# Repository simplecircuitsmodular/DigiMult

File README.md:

# DigiMult

The DigiMult features 2 DAC outputs, a trigger input, and an analog input as well as 4 potentiometers and a switch. The module can be programmed using the Arduino IDE. 

Shortly after I started designing this module, CCTV announced the Cascadence. Since my design and CCTV's were almost identical, I decided to make this module compatable with theirs. There are only 4 differences between them:
- The DigiMult is all through hole, making it easier to solder.
- The DigiMult is 8hp instead of 4hp. This is due to the larger through hole components.
- The DigiMult feaures an analog input, which is absent from the Cascadence.
- The DigiMult switch is on pin rather than pin to free up an analog pin for the input.

Information on the Cascadence can be found at [CCTV's website](https://www.cctv.fm/product-page/cascadence) and [their GitHub page](https://github.com/cctvfm/cascadence).

A template.ino and information on modifying CCTV's software to work with the DigiMult will be added soon.

## Files
### DigiMult_xx .brd and .sch
These are the board and schematic files needed to manufacture PCBs. Gerbers need to be generated in Eagle for manufacturing.

### DigiMultParts_xx.md
These are the parts lists for each module. A mouser BOM is available in this file as well.

### DigiMult.ai
These are the panels in Adobe Illustrator format. I make my panels on a laser cutter with 1/8 inch acrylic.

## Updates

### 01 07OCT19
Initial upload. Design is currently untested.

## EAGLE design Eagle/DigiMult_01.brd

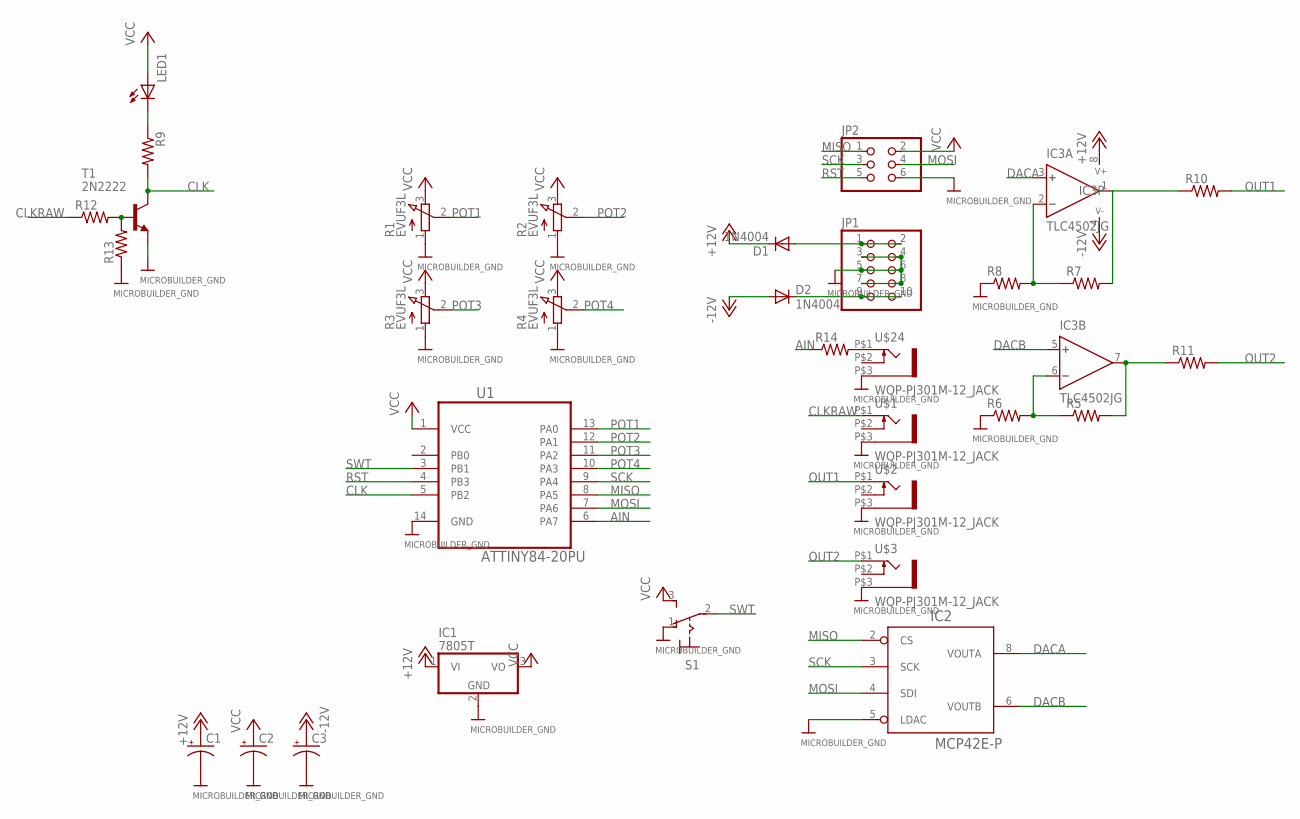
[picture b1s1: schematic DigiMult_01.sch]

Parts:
C1, C2, C3: CPOL-USE2.5-5; E2,5-5
D1, D2: 1N4004; DO41-10
IC1: 7805T; TO220H
IC2: MCP42E-P; DIL08
IC3: TLC4502JG; DIL08
JP1: PINHD-2X5/OCT; 2X05
JP2: PINHD-2X3/OCT; 2X03
LED1: LED3MM
R1, R2, R3, R4: EVUF3L; EVUFXL
R5, R6, R7, R8, R9, R10, R11, R12, R13, R14: R-US_0204/2V; 0204V
S1: M9040P
T1: 2N2222; TO92-EBC-OVAL
U1: ATTINY84-20PU; DIP254P762X533-14
U$1, U$2, U$3, U$24: WQP-PJ301M-12_JACK

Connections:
+12V: C1.+, D1.C, IC1.1 (VI), IC3.8 (V+)
-12V: C3.+, D2.A, IC3.4 (V-)
AIN: R14.1, U1.6 (PA7)
CLK: R9.2, T1.C, U1.5 (PB2)
CLKRAW: R12.1, U$1.P$1 (2)
DACA: IC2.8 (VOUTA), IC3.3 (+)
DACB: IC2.6 (VOUTB), IC3.5 (+)
GND: C1.-, C2.-, C3.-, IC1.2 (GND), IC2.5 (LDAC), IC2.7 (GND), JP1.3, JP1.4, JP1.5, JP1.6, JP1.7, JP1.8, JP2.6, R1.1 (A), R2.1 (A), R3.1 (A), R4.1 (A), R6.1, R8.1, R13.1, S1.1 (O), T1.E, U1.14 (GND), U$1.P$3 (1), U$2.P$3 (1), U$3.P$3 (1), U$24.P$3 (1)
MISO: IC2.2 (CS), JP2.1, U1.8 (PA5)
MOSI: IC2.4 (SDI), JP2.4, U1.7 (PA6)
unnamed: LED1.K (C), R9.1
unnamed: IC3.7 (OUT), R5.2, R11.1
unnamed: IC3.1 (OUT), R7.2, R10.1
unnamed: R12.2, R13.2, T1.B
unnamed: D1.A, JP1.1, JP1.2
unnamed: IC3.2 (-), R7.1, R8.2
unnamed: IC3.6 (-), R5.1, R6.2
unnamed: D2.C, JP1.9, JP1.10
unnamed: R14.2, U$24.P$1 (2)
OUT1: R10.2, U$2.P$1 (2)
OUT2: R11.2, U$3.P$1 (2)
POT1: R1.2 (S), U1.13 (PA0)
POT2: R2.2 (S), U1.12 (PA1)
POT3: R3.2 (S), U1.11 (PA2)
POT4: R4.2 (S), U1.10 (PA3)
RST: JP2.5, U1.4 (PB3)
SCK: IC2.3 (SCK), JP2.3, U1.9 (PA4)
SWT: S1.2, U1.3 (PB1)
VCC: C2.+, IC1.3 (VO), IC2.1 (VCC), JP2.2, LED1.A, R1.3 (E), R2.3 (E), R3.3 (E), R4.3 (E), S1.3 (S), U1.1 (VCC)

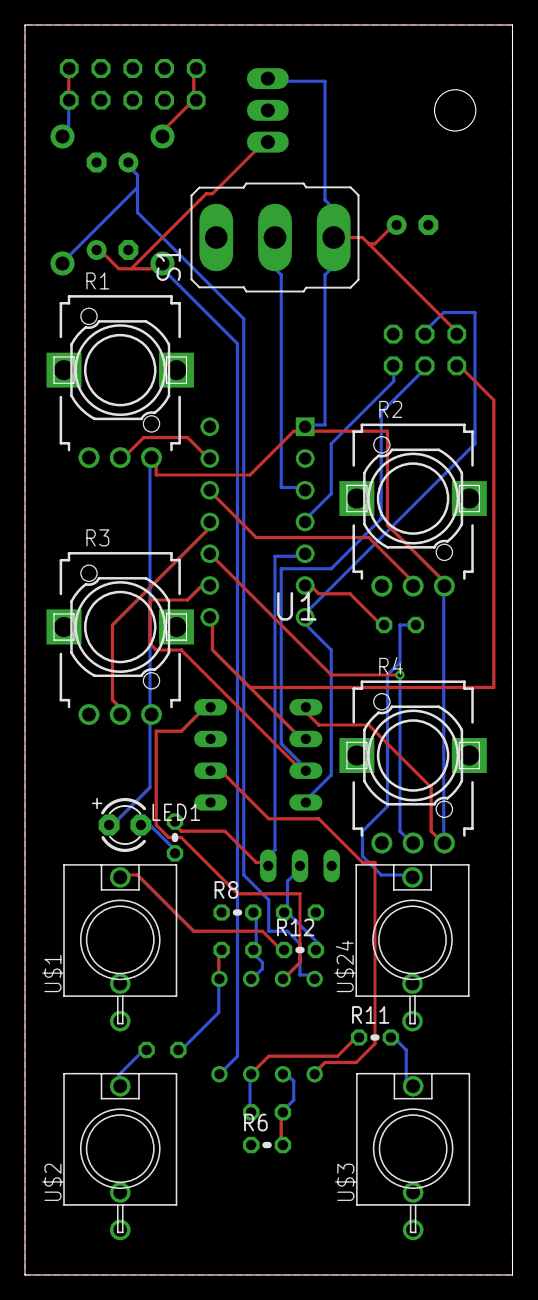
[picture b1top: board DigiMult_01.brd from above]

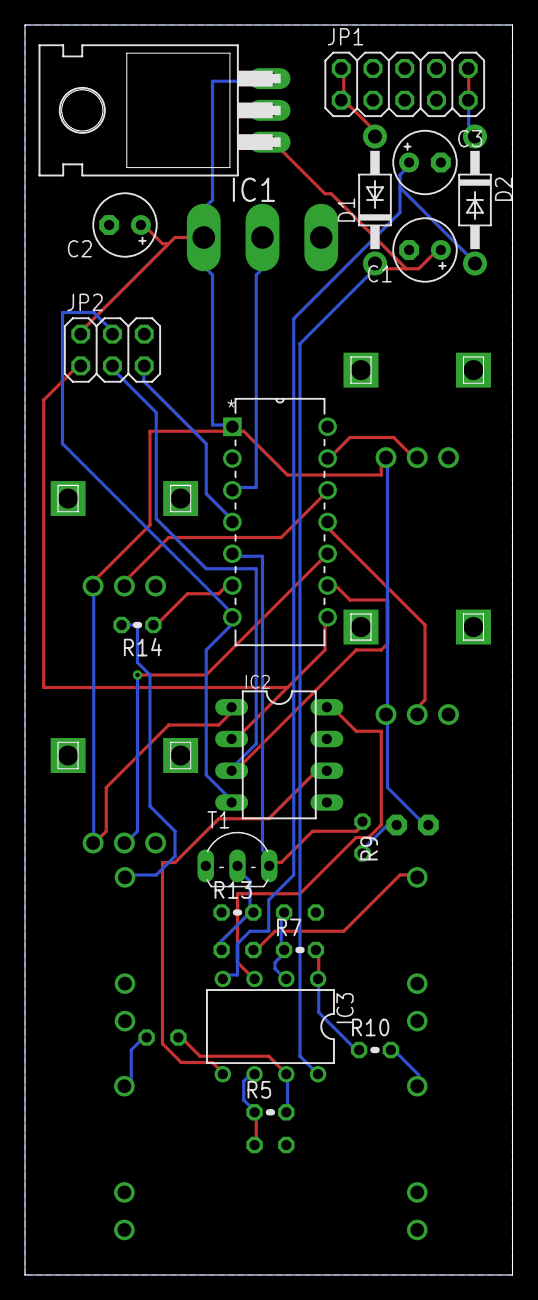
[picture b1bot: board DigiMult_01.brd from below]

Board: 2 copper layers, 39.0 x 100.0 mm, 32 parts (17 on the bottom side), 29 nets.

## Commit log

2019-10-07 Add panel outline
2019-10-08 UPdate parts list
